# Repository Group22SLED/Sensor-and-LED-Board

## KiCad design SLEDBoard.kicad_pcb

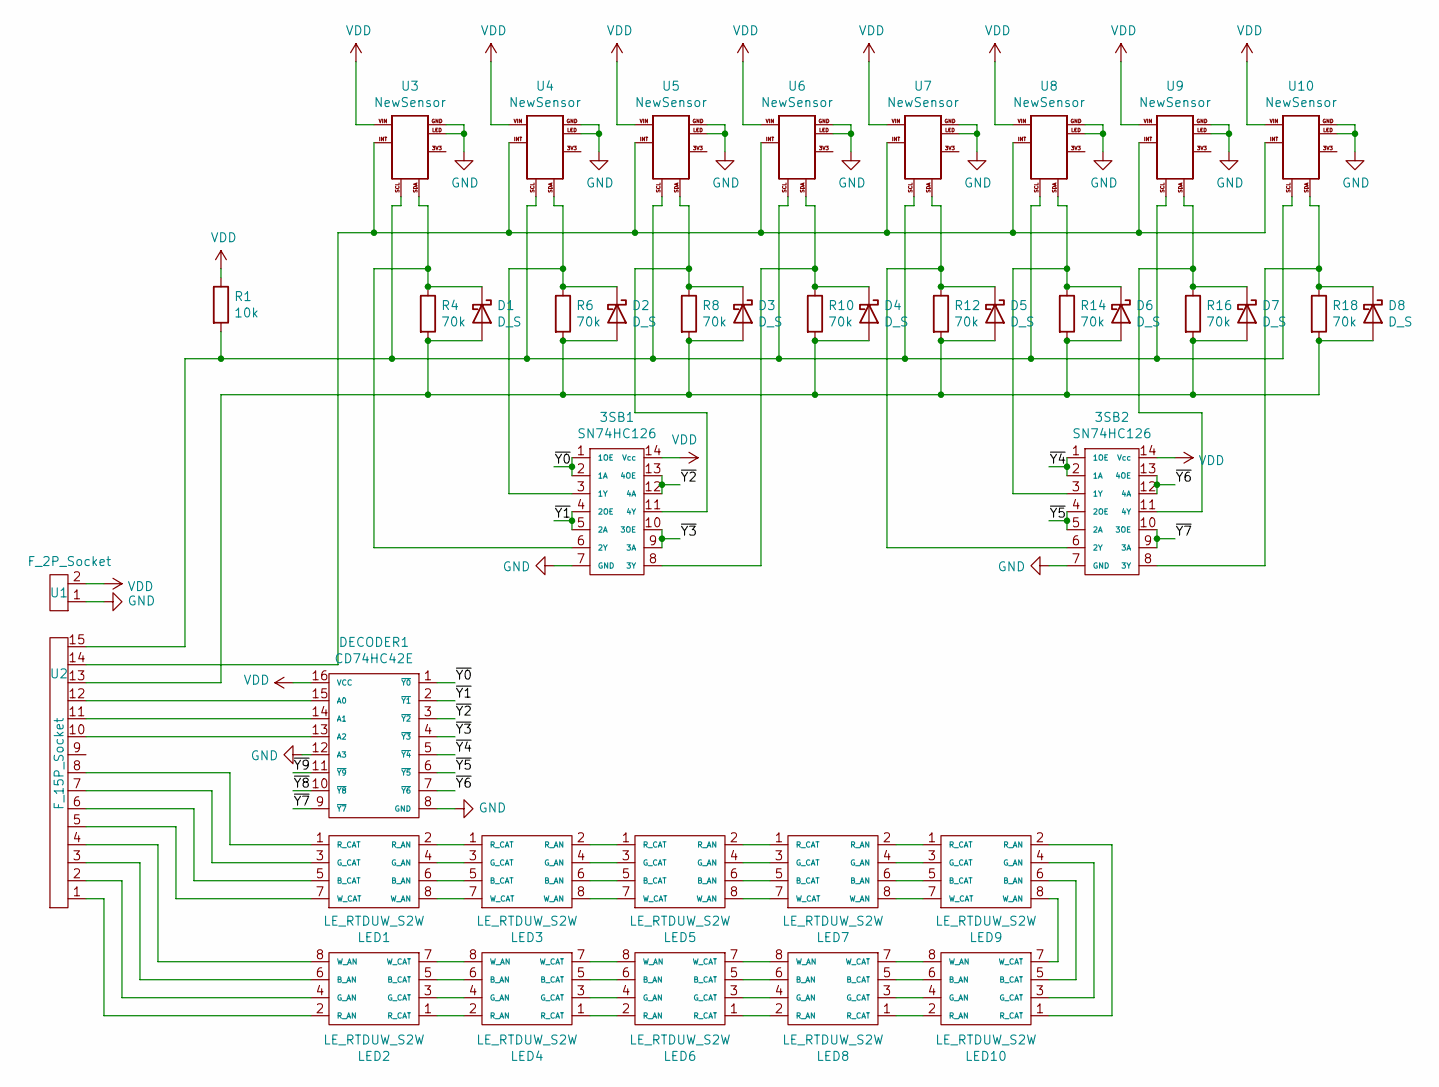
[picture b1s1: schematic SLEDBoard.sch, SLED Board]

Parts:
3SB1, 3SB2: SN74HC126; SN74HC126N
D1, D2, D3, D4, D5, D6, D7, D8: D_S; D_SOD-323
DECODER1: CD74HC42E; DIP-16_W7.62mm
LED1, LED2, LED3, LED4, LED5, LED6, LED7, LED8, LED9, LED10: LE_RTDUW_S2W
R1: 10k; R_Axial_DIN0207_L6.3mm_D2.5mm_P5.08mm_Vertical
R4, R6, R8, R10, R12, R14, R16, R18: 70k; R_0805_2012Metric
U1: F_2P_Socket; 2pin
U2: F_15P_Socket; 15pin
U3, U4, U5, U6, U7, U8, U9, U10: NewSensor

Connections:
/~Y0: 3SB1.1 (1OE), 3SB1.2 (1A), DECODER1.1 (~Y0)
/~Y1: 3SB1.4 (2OE), 3SB1.5 (2A), DECODER1.2 (~Y1)
/~Y2: 3SB1.12 (4A), 3SB1.13 (4OE), DECODER1.3 (~Y2)
/~Y3: 3SB1.9 (3A), 3SB1.10 (3OE), DECODER1.4 (~Y3)
/~Y4: 3SB2.1 (1OE), 3SB2.2 (1A), DECODER1.5 (~Y4)
/~Y5: 3SB2.4 (2OE), 3SB2.5 (2A), DECODER1.6 (~Y5)
/~Y6: 3SB2.12 (4A), 3SB2.13 (4OE), DECODER1.7 (~Y6)
/~Y7: 3SB2.9 (3A), 3SB2.10 (3OE), DECODER1.9 (~Y7)
/~Y8: DECODER1.10 (~Y8)
/~Y9: DECODER1.11 (~Y9)
GND: 3SB1.7 (GND), 3SB2.7 (GND), DECODER1.8 (GND), DECODER1.12 (A3), U1.1, U3.GND, U3.LED, U4.GND, U4.LED, U5.GND, U5.LED, U6.GND, U6.LED, U7.GND, U7.LED, U8.GND, U8.LED, U9.GND, U9.LED, U10.GND, U10.LED
unnamed: 3SB1.3 (1Y), D2.1 (K), R6.1, U4.SDA
unnamed: 3SB1.6 (2Y), D1.1 (K), R4.1, U3.SDA
unnamed: 3SB1.8 (3Y), D4.1 (K), R10.1, U6.SDA
unnamed: 3SB1.11 (4Y), D3.1 (K), R8.1, U5.SDA
unnamed: 3SB2.3 (1Y), D6.1 (K), R14.1, U8.SDA
unnamed: 3SB2.6 (2Y), D5.1 (K), R12.1, U7.SDA
unnamed: 3SB2.8 (3Y), D8.1 (K), R18.1, U10.SDA
unnamed: 3SB2.11 (4Y), D7.1 (K), R16.1, U9.SDA
unnamed: D1.2 (A), D2.2 (A), D3.2 (A), D4.2 (A), D5.2 (A), D6.2 (A), D7.2 (A), D8.2 (A), R4.2, R6.2, R8.2, R10.2, R12.2, R14.2, R16.2, R18.2, U2.13
unnamed: DECODER1.13 (A2), U2.10
unnamed: DECODER1.14 (A1), U2.11
unnamed: DECODER1.15 (A0), U2.12
unnamed: LED1.1 (R_CAT), U2.8
unnamed: LED1.2 (R_AN), LED3.1 (R_CAT)
unnamed: LED1.3 (G_CAT), U2.7
unnamed: LED1.4 (G_AN), LED3.3 (G_CAT)
unnamed: LED1.5 (B_CAT), U2.6
unnamed: LED1.6 (B_AN), LED3.5 (B_CAT)
unnamed: LED1.7 (W_CAT), U2.5
unnamed: LED1.8 (W_AN), LED3.7 (W_CAT)
unnamed: LED2.1 (R_CAT), LED4.2 (R_AN)
unnamed: LED2.2 (R_AN), U2.1
unnamed: LED2.3 (G_CAT), LED4.4 (G_AN)
unnamed: LED2.4 (G_AN), U2.2
unnamed: LED2.5 (B_CAT), LED4.6 (B_AN)
unnamed: LED2.6 (B_AN), U2.3
unnamed: LED2.7 (W_CAT), LED4.8 (W_AN)
unnamed: LED2.8 (W_AN), U2.4
unnamed: LED3.2 (R_AN), LED5.1 (R_CAT)
unnamed: LED3.4 (G_AN), LED5.3 (G_CAT)
unnamed: LED3.6 (B_AN), LED5.5 (B_CAT)
unnamed: LED3.8 (W_AN), LED5.7 (W_CAT)
unnamed: LED4.1 (R_CAT), LED6.2 (R_AN)
unnamed: LED4.3 (G_CAT), LED6.4 (G_AN)
unnamed: LED4.5 (B_CAT), LED6.6 (B_AN)
unnamed: LED4.7 (W_CAT), LED6.8 (W_AN)
unnamed: LED5.2 (R_AN), LED7.1 (R_CAT)
unnamed: LED5.4 (G_AN), LED7.3 (G_CAT)
unnamed: LED5.6 (B_AN), LED7.5 (B_CAT)
unnamed: LED5.8 (W_AN), LED7.7 (W_CAT)
unnamed: LED6.1 (R_CAT), LED8.2 (R_AN)
unnamed: LED6.3 (G_CAT), LED8.4 (G_AN)
unnamed: LED6.5 (B_CAT), LED8.6 (B_AN)
unnamed: LED6.7 (W_CAT), LED8.8 (W_AN)
unnamed: LED7.2 (R_AN), LED9.1 (R_CAT)
unnamed: LED7.4 (G_AN), LED9.3 (G_CAT)
unnamed: LED7.6 (B_AN), LED9.5 (B_CAT)
unnamed: LED7.8 (W_AN), LED9.7 (W_CAT)
unnamed: LED9.2 (R_AN), LED10.1 (R_CAT)
unnamed: LED8.1 (R_CAT), LED10.2 (R_AN)
unnamed: LED9.4 (G_AN), LED10.3 (G_CAT)
unnamed: LED8.3 (G_CAT), LED10.4 (G_AN)
unnamed: LED9.6 (B_AN), LED10.5 (B_CAT)
unnamed: LED8.5 (B_CAT), LED10.6 (B_AN)
unnamed: LED9.8 (W_AN), LED10.7 (W_CAT)
unnamed: LED8.7 (W_CAT), LED10.8 (W_AN)
unnamed: R1.2, U2.15, U3.SCL, U4.SCL, U5.SCL, U6.SCL, U7.SCL, U8.SCL, U9.SCL, U10.SCL
unnamed: U2.14, U3.INT, U4.INT, U5.INT, U6.INT, U7.INT, U8.INT, U9.INT, U10.INT
VDD: 3SB1.14 (Vcc), 3SB2.14 (Vcc), DECODER1.16 (VCC), R1.1, U1.2, U3.VIN, U4.VIN, U5.VIN, U6.VIN, U7.VIN, U8.VIN, U9.VIN, U10.VIN

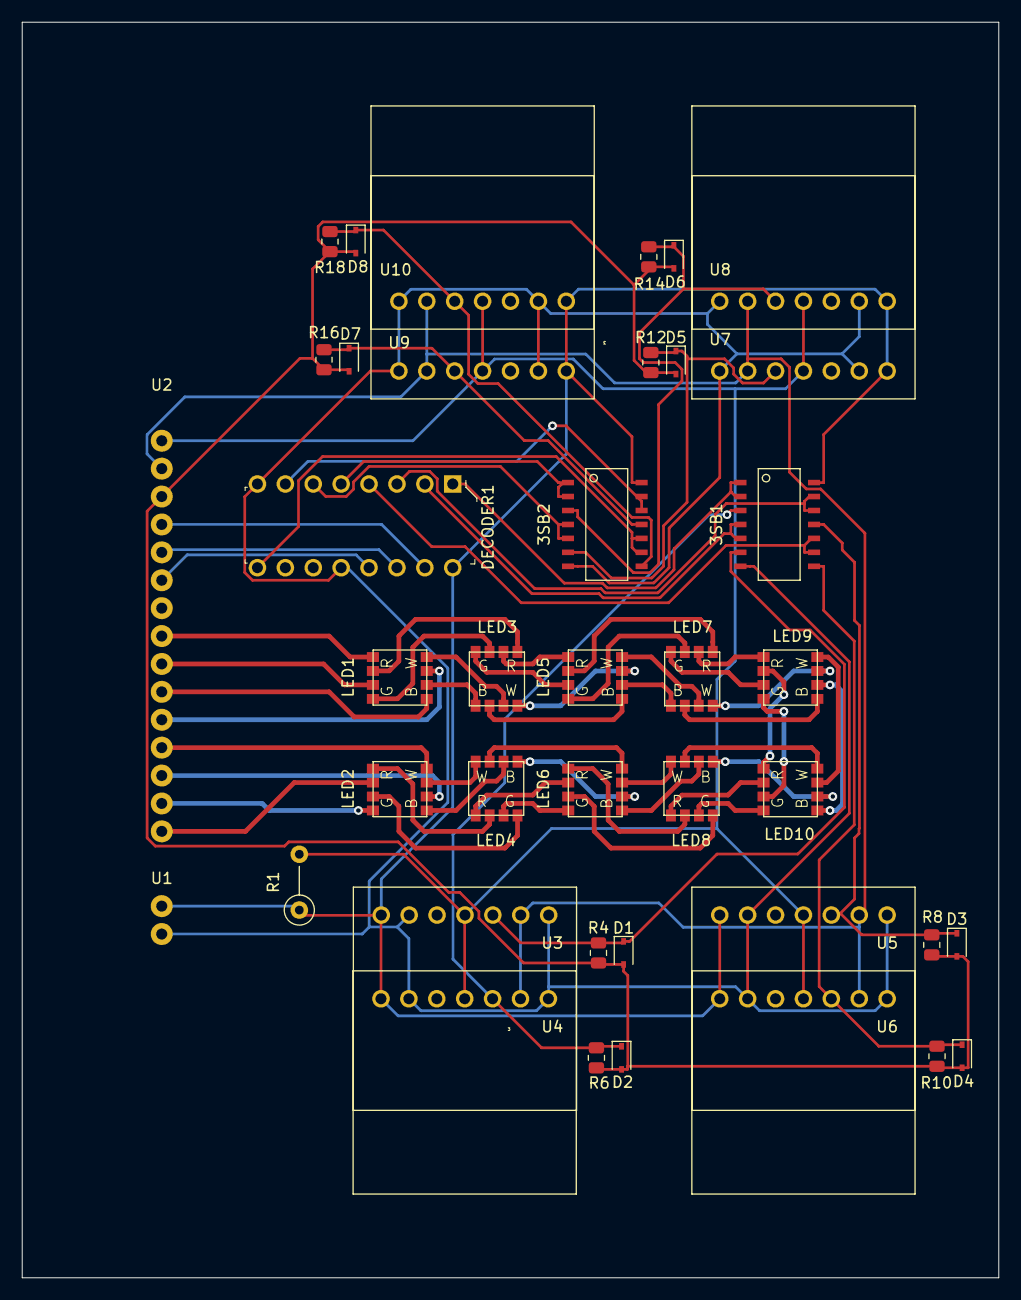
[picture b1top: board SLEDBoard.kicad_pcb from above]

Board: 2 copper layers, 88.9 x 114.3 mm, 40 parts (0 on the bottom side), 68 nets.

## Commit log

2021-01-21 KiCAD Info
    V0 of CAD
2021-01-21 Sensing and LED Board
    Previous Version missing .lib file for schematic. Couldn't find the location so uploaded all junk files too.
